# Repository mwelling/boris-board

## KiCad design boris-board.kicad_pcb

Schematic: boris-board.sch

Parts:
LD1, LD2, LD3, LD4, LD5, LD6, LD7, LD8, LD9, LD10, LD11, LD12, LD13, LD14, LD15, LD16, LD17, LD18, LD19, LD20: SK6805-2427
LOGO1: OPEN_HARDWARE_1; boris
LOGO2: OPEN_HARDWARE_1; Symbol_OSHW-Logo_SilkScreen
P1, P2: SMT-HEADER-HACK

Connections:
/(U1.A1)PWM0A: P1.36
/(U1.A2)PRU-0.1: LD1.3 (DIN), P1.33
/(U1.A3)PRU-0.4: P1.31
/(U1.A4)SPI1.CS: P2.31
/(U1.A8)AIN0~1.8V: P1.19
/(U1.A10)I2C2.SCL: P1.28
/(U1.A11)I2C1.SDA: P2.11
/(U1.A12)UART0.RX: P1.32
/(U1.A13)SPI0.CLK: P1.8
/(U1.A14)SPI0.CS: P1.6
/(U1.B1)PRU-0.3: P2.30
/(U1.B2)PRU-0.2: P2.32
/(U1.B3)PRU-0.5: P2.34
/(U1.B4)PRU-0.16: P1.20
/(U1.B6)AIN2~1.8V: P1.23
/(U1.B7)VREF+: P1.18
/(U1.B8)AIN1~1.8V: P1.21
/(U1.B9)VREF-: P1.17
/(U1.B10)I2C2.SDA: P1.26
/(U1.B11)I2C1.SCL: P2.9
/(U1.B12)UART0.TX: P1.30
/(U1.B13)SPI0.MISO: P1.10
/(U1.B14)SPI0.MOSI: P1.12
/(U1.C3)PRU-0.6: P2.28
/(U1.C4)PRU-0.7: P1.29
/(U1.C5)SPI1.CLK: P2.29
/(U1.C6)AIN3~1.8V: P1.25
/(U1.C7)AIN4~1.8V: P1.27
/(U1.C12)SPI1.MISO: P2.27
/(U1.C13)SPI1.MOSI: P2.25
/(U1.E1): P1.4
/(U1.F1): P1.35
/(U1.F2)AIN6~3.3V: P1.2
/(U1.F3)AIN5~3.3V: P2.35
/(U1.L14)USB1.ID: P1.13
/(U1.L15)USB1.D+: P1.11
/(U1.L16)USB1.D-: P1.9
/(U1.M14)USB1.DRVVBUS: P1.3
/(U1.M15)USB1.VBUS: P1.5
/(U1.N13)AIN7~1.8V: P2.36
/(U1.N14): P2.8
/(U1.P5)GPIO-0.23: P2.3
/(U1.P6): P2.24
/(U1.P7)PRU-0.15: P2.18
/(U1.P12)PWM1A: P2.1
/(U1.P15)UART4.RX: P2.5
/(U1.R5)GPIO-0.26: P1.34
/(U1.R6): P2.33
/(U1.R7): P2.20
/(U1.R11)RESET#: P2.26
/(U1.R13): P2.10
/(U1.R15): P2.4
/(U1.R16)UART4.TX: P2.7
/(U1.T5): P2.19
/(U1.T6)PRU-0.14: P2.22
/(U1.T7): P2.17
/(U1.T11)PWR.BTN: P2.12
/(U1.T15): P2.6
/(U1.T16): P2.2
/BAT.TEMP: P2.16
GND: LD1.2 (VSS), LD2.2 (VSS), LD3.2 (VSS), LD4.2 (VSS), LD5.2 (VSS), LD6.2 (VSS), LD7.2 (VSS), LD8.2 (VSS), LD9.2 (VSS), LD10.2 (VSS), LD11.2 (VSS), LD12.2 (VSS), LD13.2 (VSS), LD14.2 (VSS), LD15.2 (VSS), LD16.2 (VSS), LD17.2 (VSS), LD18.2 (VSS), LD19.2 (VSS), LD20.2 (VSS), P1.15, P1.16, P1.22, P2.15, P2.21
unnamed: LD1.1 (DOUT), LD2.3 (DIN)
unnamed: LD2.1 (DOUT), LD3.3 (DIN)
unnamed: LD3.1 (DOUT), LD4.3 (DIN)
unnamed: LD4.1 (DOUT), LD5.3 (DIN)
unnamed: LD5.1 (DOUT), LD6.3 (DIN)
unnamed: LD6.1 (DOUT), LD7.3 (DIN)
unnamed: LD7.1 (DOUT), LD8.3 (DIN)
unnamed: LD8.1 (DOUT), LD9.3 (DIN)
unnamed: LD10.1 (DOUT), LD11.3 (DIN)
unnamed: LD9.1 (DOUT), LD10.3 (DIN)
unnamed: LD11.1 (DOUT), LD12.3 (DIN)
unnamed: LD12.1 (DOUT), LD13.3 (DIN)
unnamed: LD13.1 (DOUT), LD14.3 (DIN)
unnamed: LD14.1 (DOUT), LD15.3 (DIN)
unnamed: LD15.1 (DOUT), LD16.3 (DIN)
unnamed: LD16.1 (DOUT), LD17.3 (DIN)
unnamed: LD17.1 (DOUT), LD18.3 (DIN)
unnamed: LD18.1 (DOUT), LD19.3 (DIN)
unnamed: LD19.1 (DOUT), LD20.3 (DIN)
SYS_5V: LD1.4 (VDD), LD2.4 (VDD), LD3.4 (VDD), LD4.4 (VDD), LD5.4 (VDD), LD6.4 (VDD), LD7.4 (VDD), LD8.4 (VDD), LD9.4 (VDD), LD10.4 (VDD), LD11.4 (VDD), LD12.4 (VDD), LD13.4 (VDD), LD14.4 (VDD), LD15.4 (VDD), LD16.4 (VDD), LD17.4 (VDD), LD18.4 (VDD), LD19.4 (VDD), LD20.4 (VDD), P1.24, P2.13
USB_DC: P1.7
VDD_3V3B: P2.23
VDD_5V: P1.1
VIN.BAT: P2.14

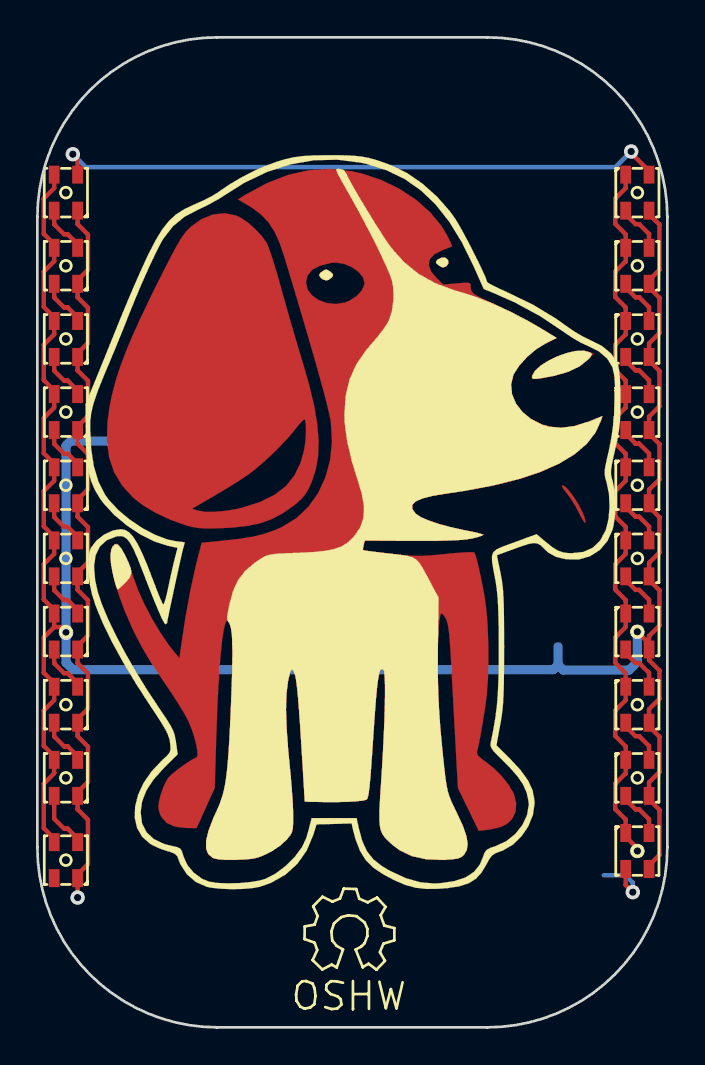
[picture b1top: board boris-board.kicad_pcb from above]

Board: 4 copper layers, 35.0 x 55.0 mm, 24 parts (0 on the bottom side), 22 nets.

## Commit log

2017-09-06 Initial commit of the Boris Board
    Little demo board for new PocketBeagle design.
2017-09-12 Add some stuff
2019-09-24 Update to KiCAD 5
